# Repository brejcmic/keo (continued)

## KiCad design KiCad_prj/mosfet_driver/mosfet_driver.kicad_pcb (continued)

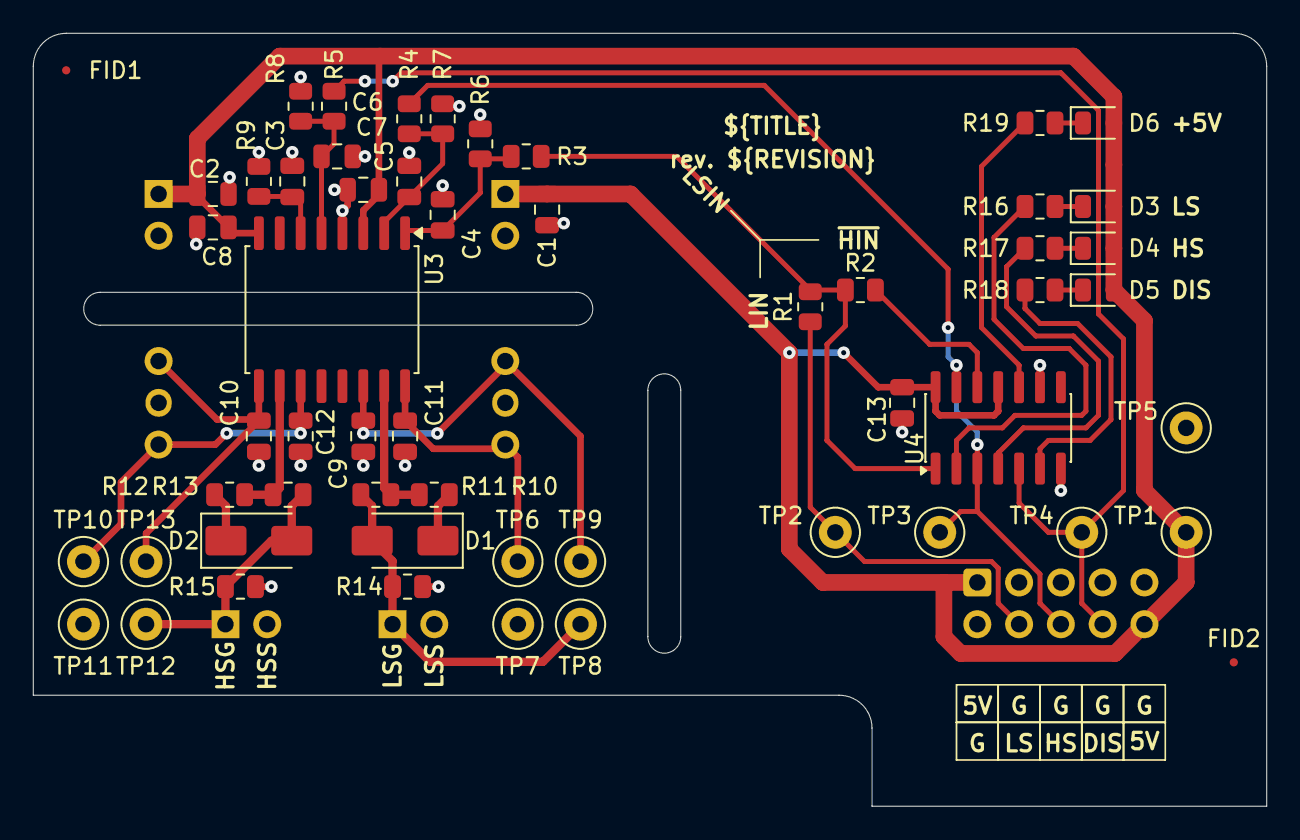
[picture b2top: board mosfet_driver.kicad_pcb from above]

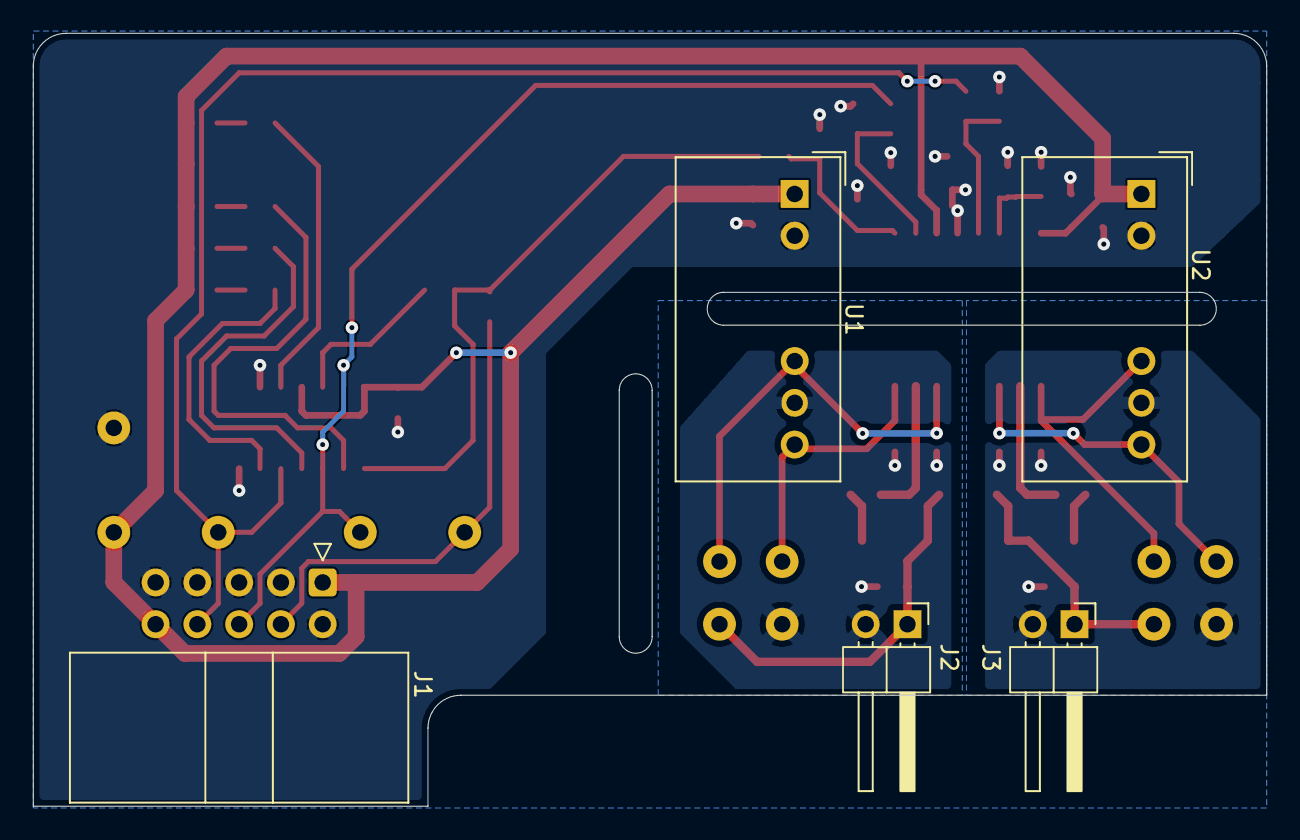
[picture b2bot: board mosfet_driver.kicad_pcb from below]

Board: 2 copper layers, 75.0 x 47.0 mm, 60 parts (5 on the bottom side), 31 nets.

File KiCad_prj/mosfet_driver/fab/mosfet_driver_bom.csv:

"Comment","Designator","Footprint","JLCPCB Part #"
"100n","C1,C2,C13","Capacitor_SMD:C_0805_2012Metric","C28233"
"470p","C3","Capacitor_SMD:C_0805_2012Metric","C1743"
"22p","C4,C5,C6","Capacitor_SMD:C_0805_2012Metric","C1804"
"1u","C7,C8,C9,C10,C11,C12","Capacitor_SMD:C_0805_2012Metric","C28323"
"SS14","D1,D2","Diode_SMD:D_SMA","C2480"
"RED","D3,D4,D5,D6,D7","LED_SMD:LED_0805_2012Metric","C84256"
"0R","R1,R2","Resistor_SMD:R_0805_2012Metric","C17477"
"100R","R3,R4,R5","Resistor_SMD:R_0805_2012Metric","C17408"
"10k","R6,R7,R8,R14,R15","Resistor_SMD:R_0805_2012Metric","C17414"
"47k","R9","Resistor_SMD:R_0805_2012Metric","C17713"
"3R3","R10,R12","Resistor_SMD:R_0805_2012Metric","C16257"
"10R","R11,R13","Resistor_SMD:R_0805_2012Metric","C17415"
"1k","R16,R17,R18,R19,R20","Resistor_SMD:R_0805_2012Metric","C17513"
"UCC21520ADW","U3","Package_SO:SOIC-16W_7.5x10.3mm_P1.27mm","C2863027"
"74HC14","U4","Package_SO:SOIC-14_3.9x8.7mm_P1.27mm","C5605"

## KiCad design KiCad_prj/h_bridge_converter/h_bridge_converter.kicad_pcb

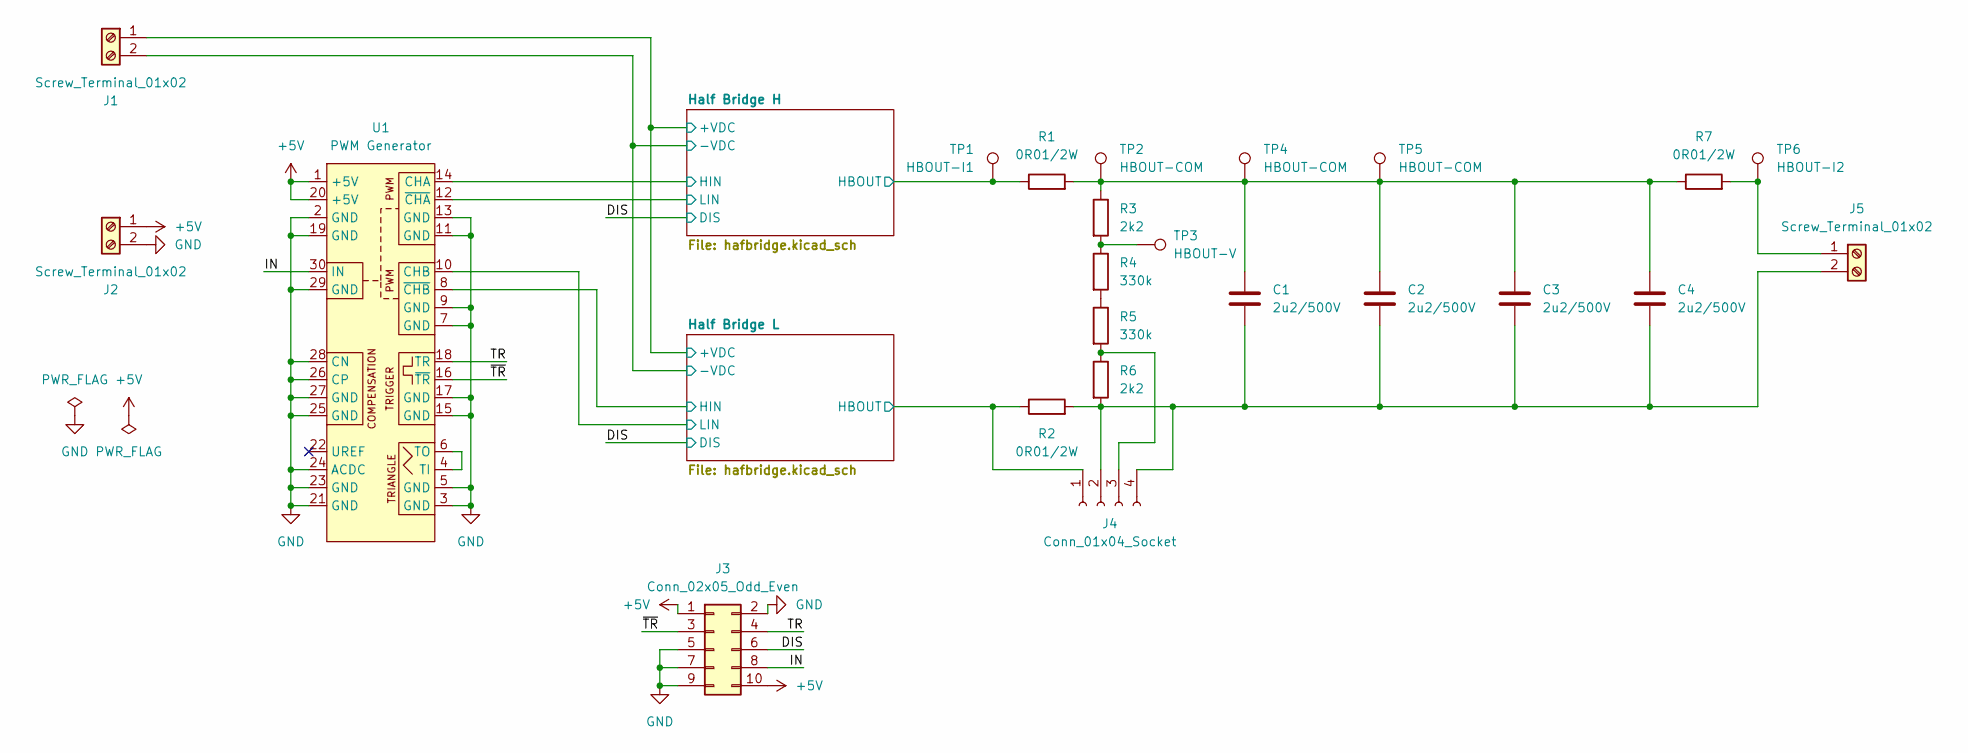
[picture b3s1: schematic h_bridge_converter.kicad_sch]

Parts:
C1, C2, C3, C4: 2u2/500V; C_Rect_L31.5mm_W13.0mm_P27.50mm_MKS4
J1, J2, J5: Screw_Terminal_01x02; TerminalBlock_WAGO_236-502_1x02_P7.50mm_45Degree
J3: Conn_02x05_Odd_Even; PinSocket_2x05_P2.54mm_Vertical
J4: Conn_01x04_Socket; PinSocket_1x04_P2.54mm_Vertical
R1, R2, R7: 0R01/2W; R_Axial_DIN0309_L9.0mm_D3.2mm_P15.24mm_Horizontal
R3, R6: 2k2; R_Axial_DIN0207_L6.3mm_D2.5mm_P7.62mm_Horizontal
R4, R5: 330k; R_Axial_DIN0207_L6.3mm_D2.5mm_P7.62mm_Horizontal
TP1: HBOUT-I1; TestPoint_Bridge_Pitch2.54mm_Drill1.0mm
TP2, TP4, TP5: HBOUT-COM; TestPoint_Bridge_Pitch2.54mm_Drill1.0mm
TP3: HBOUT-V; TestPoint_Bridge_Pitch2.54mm_Drill1.0mm
TP6: HBOUT-I2; TestPoint_Bridge_Pitch2.54mm_Drill1.0mm
U1: PWM Generator; PWMGeneratorKEO

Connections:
+5V: J2.1, J3.1, J3.10, U1.1 (+5V), U1.20 (+5V); also elsewhere on the board
/DIS: J3.6; also elsewhere on the board
/Half Bridge H/+VDC: J1.1; also elsewhere on the board
/Half Bridge H/-VDC: J1.2; also elsewhere on the board
/Half Bridge H/HBOUT: R1.1, TP1.1 (1_1); also elsewhere on the board
/Half Bridge H/HIN: U1.14 (CHA); also elsewhere on the board
/Half Bridge H/LIN: U1.12 (~CHA); also elsewhere on the board
/Half Bridge L/HBOUT: J4.1, R2.1; also elsewhere on the board
/Half Bridge L/HIN: U1.8 (~CHB); also elsewhere on the board
/Half Bridge L/LIN: U1.10 (CHB); also elsewhere on the board
/IN: J3.8, U1.30 (IN)
/TR: J3.4, U1.18 (TR)
/~TR: J3.3, U1.16 (~TR)
GND: J2.2, J3.2, J3.5, J3.7, J3.9, U1.2 (GND), U1.3 (GND), U1.5 (GND), U1.7 (GND), U1.9 (GND), U1.11 (GND), U1.13 (GND), U1.15 (GND), U1.17 (GND), U1.19 (GND), U1.21 (GND), U1.23 (GND), U1.24 (ACDC), U1.25 (GND), U1.26 (CP), U1.27 (GND), U1.28 (CN), U1.29 (GND); also elsewhere on the board
unnamed: C1.1, C2.1, C3.1, C4.1, R1.2, R3.1, R7.1, TP2.1 (1_1), TP4.1 (1_1), TP5.1 (1_1)
unnamed: C1.2, C2.2, C3.2, C4.2, J4.2, J4.4, J5.2, R2.2, R6.2
unnamed: J4.3, R5.2, R6.1
unnamed: J5.1, R7.2, TP6.1 (1_1)
unnamed: R3.2, R4.1, TP3.1 (1_1)
unnamed: R4.2, R5.1
unnamed: U1.4 (TI), U1.6 (TO)

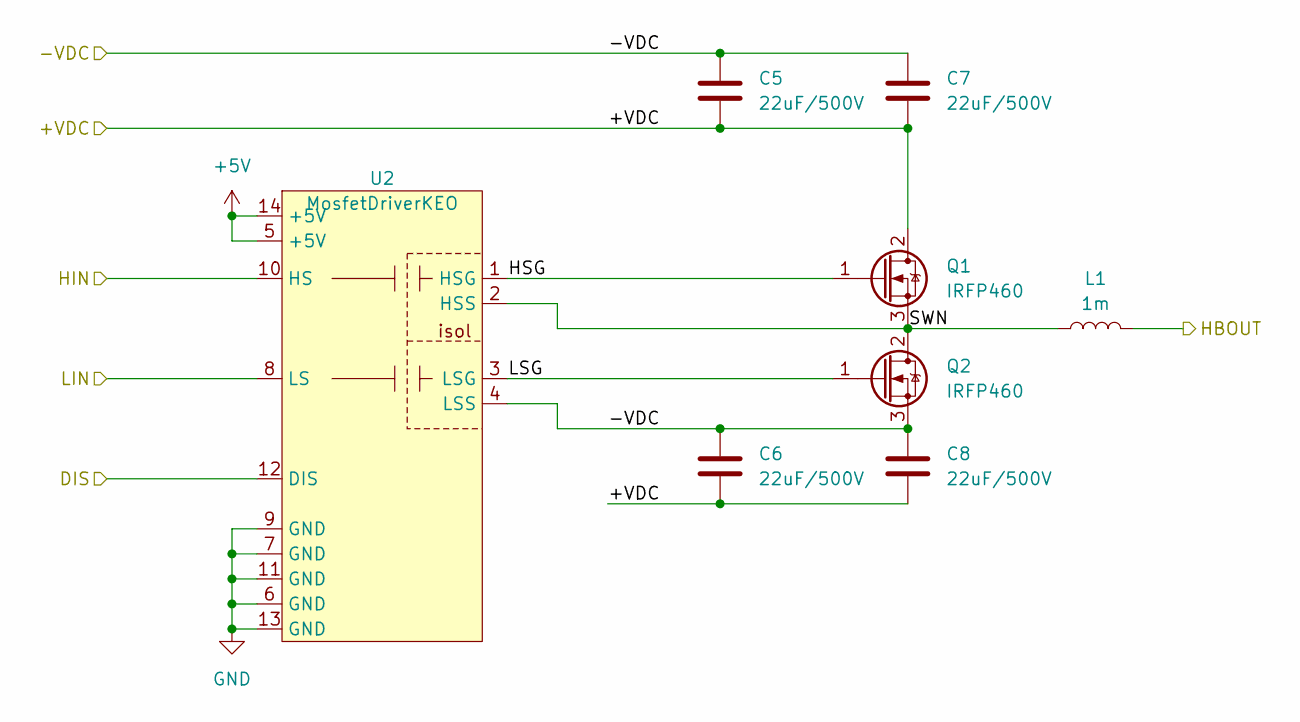
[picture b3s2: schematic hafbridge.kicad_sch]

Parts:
C5, C6, C7, C8: 22uF/500V; C_Rect_L31.5mm_W20.0mm_P27.50mm_MKS4
L1: 1m; L_Toroid_Vertical_L54.0mm_W23.8mm_P20.10mm_Bourns_5700
Q1, Q2: IRFP460; TO-247-3_Horizontal
U2: MosfetDriverKEO; Mosfet_Driver_KEO

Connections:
+5V: U2.5 (+5V), U2.14 (+5V); also elsewhere on the board
/DIS: U2.12 (DIS); also elsewhere on the board
/Half Bridge H/+VDC: C5.2, C6.2, C7.2, C8.2, Q1.2 (D); also elsewhere on the board
/Half Bridge H/-VDC: C5.1, C6.1, C7.1, C8.1, Q2.3 (S), U2.4 (LSS); also elsewhere on the board
/Half Bridge H/HBOUT: L1.2; also elsewhere on the board
/Half Bridge H/HIN: U2.10 (HS); also elsewhere on the board
/Half Bridge H/HSG: Q1.1 (G), U2.1 (HSG)
/Half Bridge H/LIN: U2.8 (LS); also elsewhere on the board
/Half Bridge H/LSG: Q2.1 (G), U2.3 (LSG)
/Half Bridge H/SWN: L1.1, Q1.3 (S), Q2.2 (D), U2.2 (HSS)
GND: U2.6 (GND), U2.7 (GND), U2.9 (GND), U2.11 (GND), U2.13 (GND); also elsewhere on the board

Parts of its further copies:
C9, C10, C11, C12: 22uF/500V; C_Rect_L31.5mm_W20.0mm_P27.50mm_MKS4
L2: 1m; L_Toroid_Vertical_L54.0mm_W23.8mm_P20.10mm_Bourns_5700
Q3, Q4: IRFP460; TO-247-3_Horizontal
U3: MosfetDriverKEO; Mosfet_Driver_KEO

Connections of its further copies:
+5V: U3.5 (+5V), U3.14 (+5V); also elsewhere on the board
/DIS: U3.12 (DIS); also elsewhere on the board
/Half Bridge H/+VDC: C9.2, C10.2, C11.2, C12.2, Q3.2 (D); also elsewhere on the board
/Half Bridge H/-VDC: C9.1, C10.1, C11.1, C12.1, Q4.3 (S), U3.4 (LSS); also elsewhere on the board
/Half Bridge L/HBOUT: L2.2; also elsewhere on the board
/Half Bridge L/HIN: U3.10 (HS); also elsewhere on the board
/Half Bridge L/HSG: Q3.1 (G), U3.1 (HSG)
/Half Bridge L/LIN: U3.8 (LS); also elsewhere on the board
/Half Bridge L/LSG: Q4.1 (G), U3.3 (LSG)
/Half Bridge L/SWN: L2.1, Q3.3 (S), Q4.2 (D), U3.2 (HSS)
GND: U3.6 (GND), U3.7 (GND), U3.9 (GND), U3.11 (GND), U3.13 (GND); also elsewhere on the board

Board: 2 copper layers, 39 parts (4 on the bottom side), 27 nets, no tracks yet.

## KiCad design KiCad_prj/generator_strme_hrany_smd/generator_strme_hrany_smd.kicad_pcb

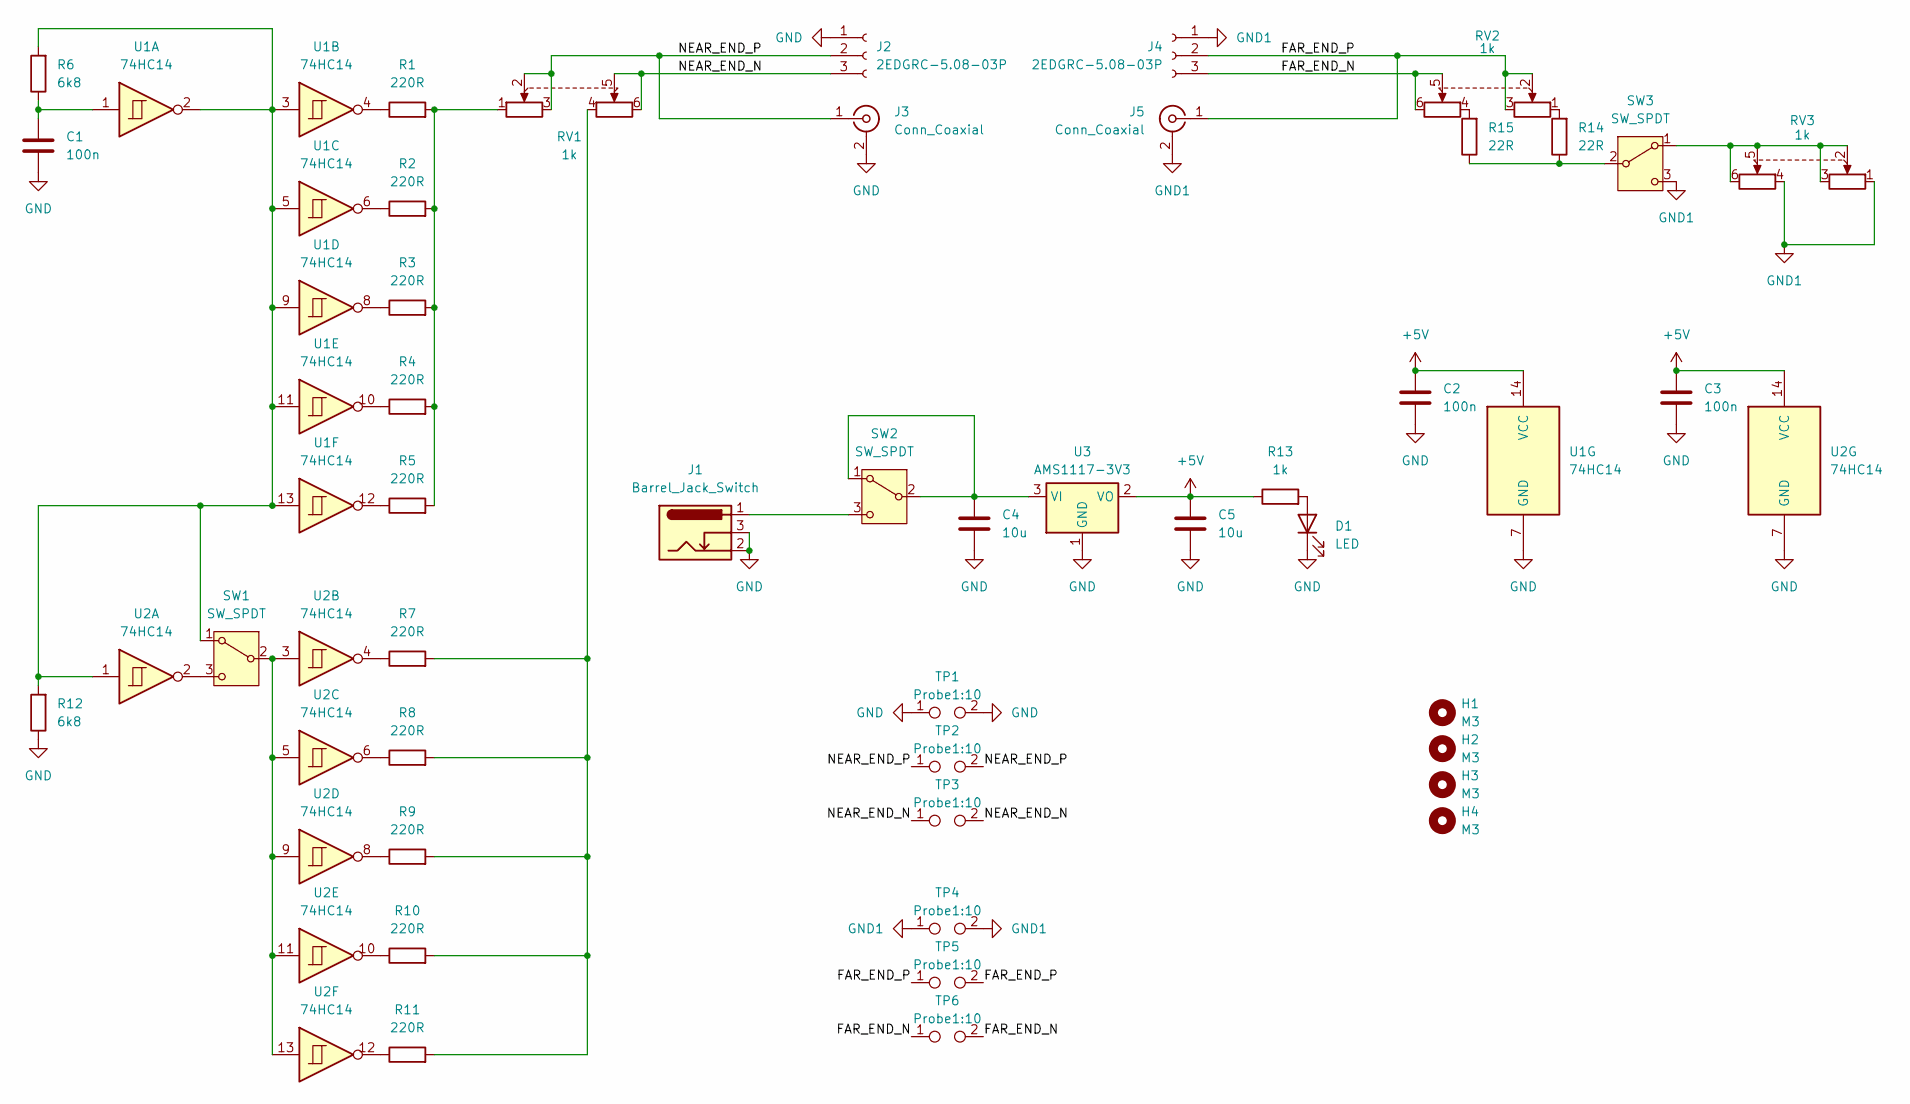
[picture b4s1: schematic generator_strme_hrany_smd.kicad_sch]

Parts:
C1, C2, C3: 100n; C_0805_2012Metric
C4, C5: 10u; C_0805_2012Metric
D1: LED; LED_0805_2012Metric
H1, H2, H3, H4: M3; MountingHole_3.2mm_M3_ISO7380
J1: Barrel_Jack_Switch; BarrelJack_GCT_DCJ200-10-A_Horizontal
J2, J4: 2EDGRC-5.08-03P; PhoenixContact_MSTBA_2,5_3-G-5,08_1x03_P5.08mm_Horizontal
J3, J5: Conn_Coaxial; BNC_Amphenol_B6252HB-NPP3G-50_Horizontal
R1, R2, R3, R4, R5, R7, R8, R9, R10, R11: 220R; R_0805_2012Metric
R6, R12: 6k8; R_0805_2012Metric
R13: 1k; R_0805_2012Metric
R14, R15: 22R; R_0805_2012Metric
RV1, RV2, RV3: 1k; Potentiometer_Alpha_RD902F-40-00D_Dual_Vertical
SW1, SW2, SW3: SW_SPDT; KLS7-SS02-12F20
TP1, TP2, TP3, TP4, TP5, TP6: Probe1:10; TestPoint_2Pads_Pitch2.54mm_Drill0.8mm
U1, U2: 74HC14; DIP-14_W7.62mm_LongPads
U3: AMS1117-3V3; SOT-223-3_TabPin2

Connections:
+5V: C2.1, C3.1, C5.1, R13.1, U1.14 (VCC), U2.14 (VCC), U3.2 (VO)
/FAR_END_N: J4.3, RV2.5, RV2.6, TP6.1, TP6.2
/FAR_END_P: J4.2, J5.1 (In), RV2.2, RV2.3, TP5.1, TP5.2
/NEAR_END_N: J2.3, RV1.5, RV1.6, TP3.1, TP3.2
/NEAR_END_P: J2.2, J3.1 (In), RV1.2, RV1.3, TP2.1, TP2.2
GND: C1.2, C2.2, C3.2, C4.2, C5.2, D1.1 (K), J1.2, J1.3, J2.1, J3.2 (Ext), R12.1, TP1.1, TP1.2, U1.7 (GND), U2.7 (GND), U3.1 (GND)
GND1: J4.1, J5.2 (Ext), RV3.1, RV3.4, SW3.3 (C), TP4.1, TP4.2
unnamed: C1.1, R6.1, U1.1
unnamed: D1.2 (A), R13.2
unnamed: R1.1, U1.4
unnamed: R1.2, R2.2, R3.2, R4.2, R5.2, RV1.1
unnamed: R2.1, U1.6
unnamed: R3.1, U1.8
unnamed: R4.1, U1.10
unnamed: R5.1, U1.12
unnamed: R7.1, U2.4
unnamed: R8.1, U2.6
unnamed: R9.1, U2.8
unnamed: R10.1, U2.10
unnamed: R7.2, R8.2, R9.2, R10.2, R11.2, RV1.4
unnamed: R11.1, U2.12
unnamed: R14.2, RV2.1
unnamed: R15.2, RV2.4
unnamed: R6.2, R12.2, SW1.1 (A), U1.2, U1.3, U1.5, U1.9, U1.11, U1.13, U2.1
unnamed: SW1.2 (B), U2.3, U2.5, U2.9, U2.11, U2.13
unnamed: SW1.3 (C), U2.2
unnamed: C4.1, SW2.1 (A), SW2.2 (B), U3.3 (VI)
unnamed: J1.1, SW2.3 (C)
unnamed: RV3.2, RV3.3, RV3.5, RV3.6, SW3.1 (A)
unnamed: R14.1, R15.1, SW3.2 (B)

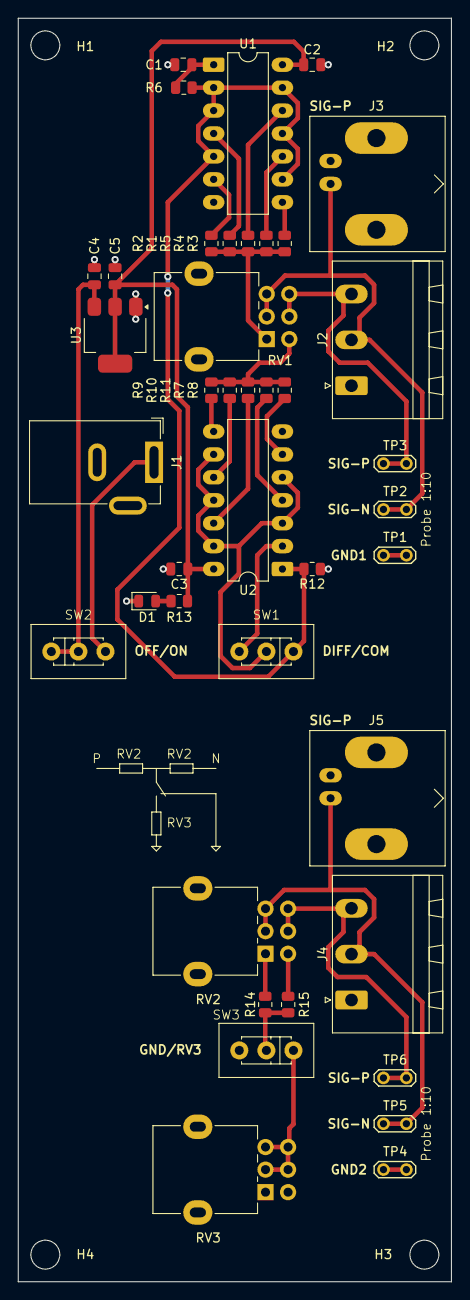
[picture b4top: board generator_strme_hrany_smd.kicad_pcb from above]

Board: 2 copper layers, 48.0 x 140.0 mm, 45 parts (0 on the bottom side), 30 nets.

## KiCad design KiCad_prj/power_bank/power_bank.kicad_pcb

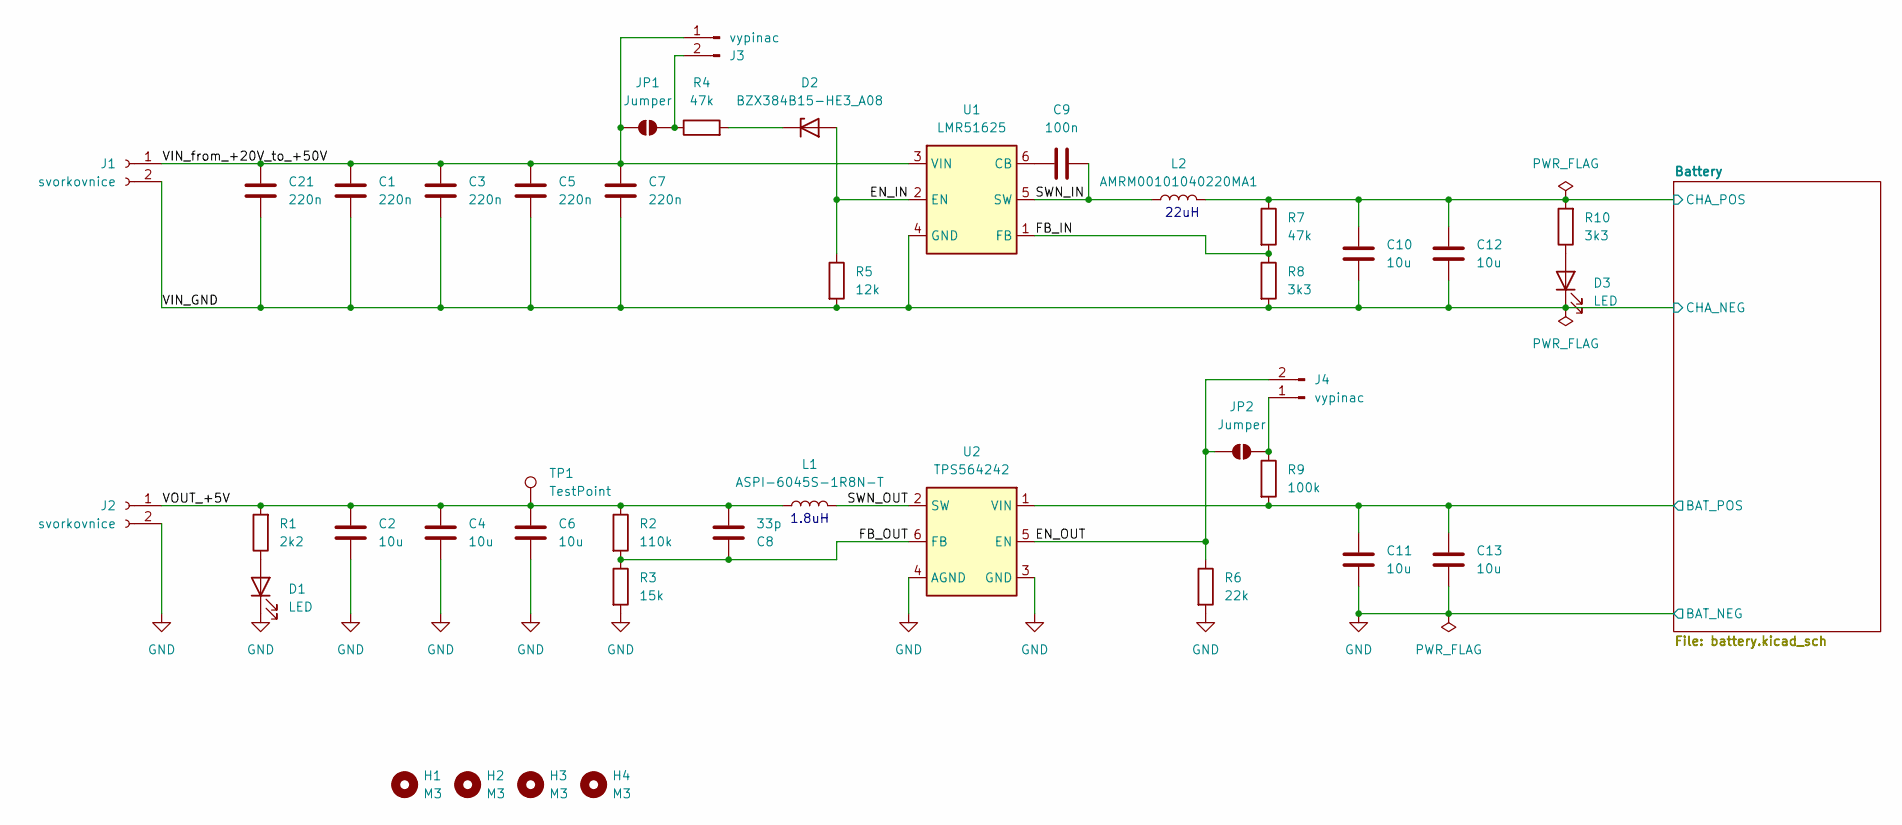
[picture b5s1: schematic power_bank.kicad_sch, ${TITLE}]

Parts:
C1, C3, C5, C7, C21: 220n; C_0805_2012Metric; JLCPCB Part # C6119933
C2, C4, C6, C10, C11, C12, C13: 10u; C_0805_2012Metric; JLCPCB Part # C15850
C8: 33p; C_0805_2012Metric; JLCPCB Part # C107115
C9: 100n; C_0805_2012Metric; JLCPCB Part # C28233
D1, D3: LED; LED_D3.0mm
D2: BZX384B15-HE3_A08; D_SOD-323F; JLCPCB Part # C49296788
H1, H2, H3, H4: M3; MountingHole_3.2mm_M3
J1, J2: svorkovnice; PhoenixContact_MSTBVA_2,5_2-G-5,08_1x02_P5.08mm_Vertical
J3, J4: vypinac; PinHeader_1x02_P2.54mm_Vertical
JP1, JP2: Jumper; SolderJumper-2_P1.3mm_Open_RoundedPad1.0x1.5mm
L1: ASPI-6045S-1R8N-T; L_APV_ANR6045; JLCPCB Part # C2997654
L2: AMRM00101040220MA1; L_10.4x10.4_H4.8; JLCPCB Part # C10165
R1: 2k2; R_0805_2012Metric; JLCPCB Part # C17520
R2: 110k; R_0805_2012Metric; JLCPCB Part # C17422
R3: 15k; R_0805_2012Metric; JLCPCB Part # C17475
R4, R7: 47k; R_0805_2012Metric; JLCPCB Part # C17713
R5: 12k; R_0805_2012Metric; JLCPCB Part # C17444
R6: 22k; R_0805_2012Metric; JLCPCB Part # C17560
R8, R10: 3k3; R_0805_2012Metric; JLCPCB Part # C26010
R9: 100k; R_0805_2012Metric; JLCPCB Part # C149504
TP1: TestPoint; TestPoint_Pad_D2.0mm
U1: LMR51625; SOT-23-6; JLCPCB Part # C45262767
U2: TPS564242; SOT-563; JLCPCB Part # C5219267

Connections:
/Battery/BAT_POS: C11.1, C13.1, R9.2, U2.1 (VIN); also elsewhere on the board
/Battery/CHA_POS: C10.1, C12.1, L2.2, R7.1, R10.2; also elsewhere on the board
/EN_IN: D2.2 (A), R5.1, U1.2 (EN)
/EN_OUT: J4.2, JP2.1 (A), R6.1, U2.5 (EN)
/FB_IN: R7.2, R8.1, U1.1 (FB)
/FB_OUT: C8.2, R2.2, R3.1, U2.6 (FB)
/SWN_IN: C9.2, L2.1, U1.5 (SW)
/SWN_OUT: L1.2, U2.2 (SW)
/VIN_GND: C1.2, C3.2, C5.2, C7.2, C10.2, C12.2, C21.2, D3.1 (K), J1.2, R5.2, R8.2, U1.4 (GND); also elsewhere on the board
/VIN_from_+20V_to_+50V: C1.1, C3.1, C5.1, C7.1, C21.1, J1.1, J3.1, JP1.1 (A), U1.3 (VIN)
/VOUT_+5V: C2.1, C4.1, C6.1, C8.1, J2.1, L1.1, R1.2, R2.1, TP1.1
GND: C2.2, C4.2, C6.2, C11.2, C13.2, D1.1 (K), J2.2, R3.2, R6.2, U2.3 (GND), U2.4 (AGND); also elsewhere on the board
unnamed: D1.2 (A), R1.1
unnamed: D2.1 (K), R4.2
unnamed: D3.2 (A), R10.1
unnamed: J3.2, JP1.2 (B), R4.1
unnamed: J4.1, JP2.2 (B), R9.1
unnamed: C9.1, U1.6 (CB)

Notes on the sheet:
1.8uH
22uH

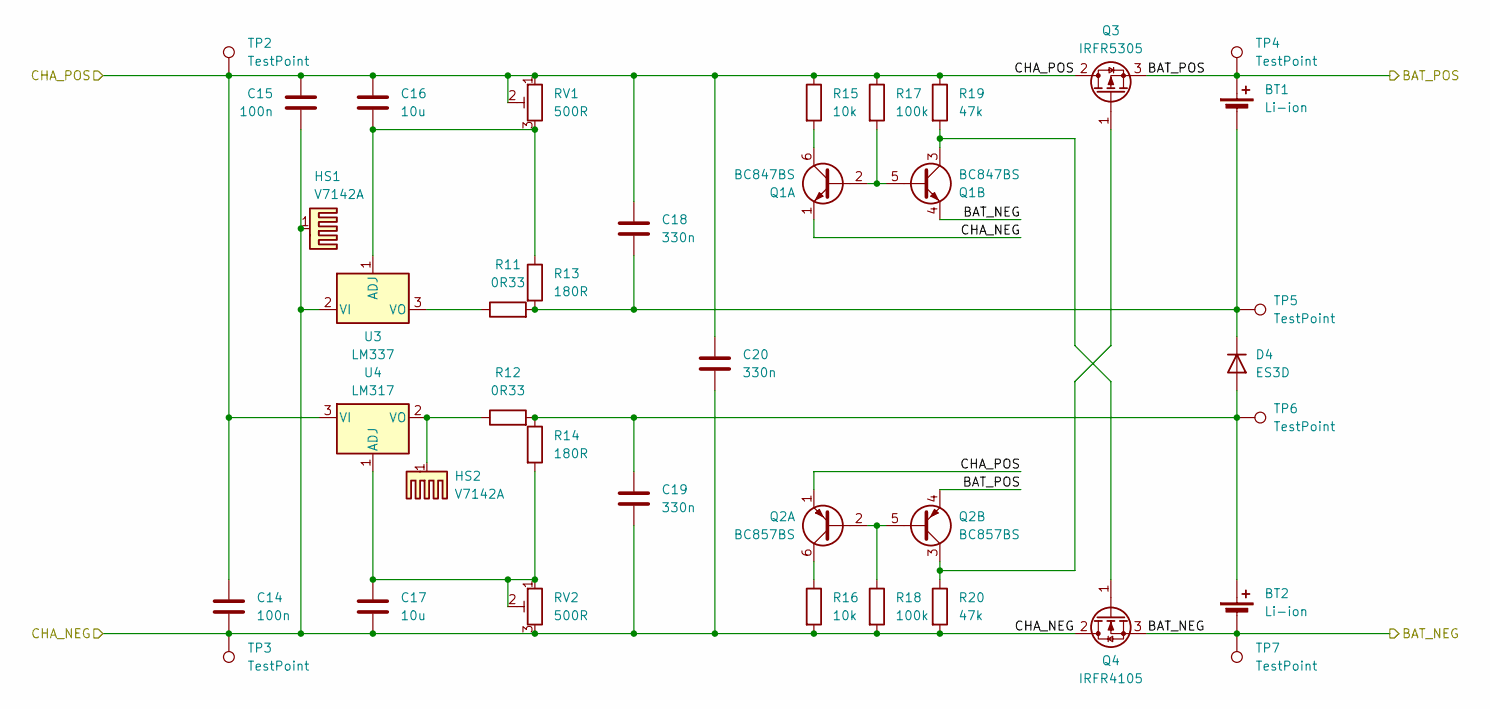
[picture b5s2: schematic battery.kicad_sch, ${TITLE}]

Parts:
BT1, BT2: Li-ion; BatteryHolder_MPD_BH-18650-PC
C14, C15: 100n; C_0805_2012Metric; JLCPCB Part # C28233
C16, C17: 10u; C_0805_2012Metric; JLCPCB Part # C15850
C18, C19, C20: 330n; C_0805_2012Metric; JLCPCB Part # C1740
D4: ES3D; D_SMC; JLCPCB Part # C16235
HS1, HS2: V7142A
Q1: BC847BS; SOT-363_SC-70-6; JLCPCB Part # C8653
Q2: BC857BS; SOT-363_SC-70-6; JLCPCB Part # C8654
Q3: IRFR5305; TO-252-2; JLCPCB Part # C2624
Q4: IRFR4105; TO-252-2; JLCPCB Part # C22366766
R11, R12: 0R33; R_Axial_DIN0411_L9.9mm_D3.6mm_P12.70mm_Horizontal
R13, R14: 180R; R_0805_2012Metric; JLCPCB Part # C1339
R15, R16: 10k; R_0805_2012Metric; JLCPCB Part # C17414
R17, R18: 100k; R_0805_2012Metric; JLCPCB Part # C149504
R19, R20: 47k; R_0805_2012Metric; JLCPCB Part # C17713
RV1, RV2: 500R; Potentiometer_ACP_CA9-V10_Vertical
TP2, TP3, TP4, TP5, TP6, TP7: TestPoint; TestPoint_Pad_D2.0mm
U3: LM337; TO-220-3_Vertical
U4: LM317; TO-220-3_Vertical

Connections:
/Battery/BAT_POS: BT1.1 (+), Q2.4 (E2), Q3.3 (S), TP4.1; also elsewhere on the board
/Battery/CHA_POS: C14.1, C15.1, C16.1, C18.1, C20.1, Q2.1 (E1), Q3.2 (D), R15.1, R17.1, R19.1, RV1.1, RV1.2, TP2.1, U4.3 (VI); also elsewhere on the board
/VIN_GND: C14.2, C15.2, C17.2, C19.2, C20.2, HS1.1, Q1.1 (E1), Q4.2 (D), R16.2, R18.2, R20.2, RV2.3, TP3.1, U3.2 (VI); also elsewhere on the board
GND: BT2.2 (-), Q1.4 (E2), Q4.3 (S), TP7.1; also elsewhere on the board
unnamed: BT1.2 (-), C18.2, D4.1 (K), R11.2, R13.2, TP5.1
unnamed: BT2.1 (+), C19.1, D4.2 (A), R12.2, R14.1, TP6.1
unnamed: Q1.2 (B1), Q1.5 (B2), R17.2
unnamed: Q1.6 (C1), R15.2
unnamed: Q1.3 (C2), Q4.1 (G), R19.2
unnamed: Q2.2 (B1), Q2.5 (B2), R18.1
unnamed: Q2.6 (C1), R16.1
unnamed: Q2.3 (C2), Q3.1 (G), R20.1
unnamed: C16.2, R13.1, RV1.3, U3.1 (ADJ)
unnamed: R11.1, U3.3 (VO)
unnamed: C17.1, R14.2, RV2.1, RV2.2, U4.1 (ADJ)
unnamed: HS2.1, R12.1, U4.2 (VO)

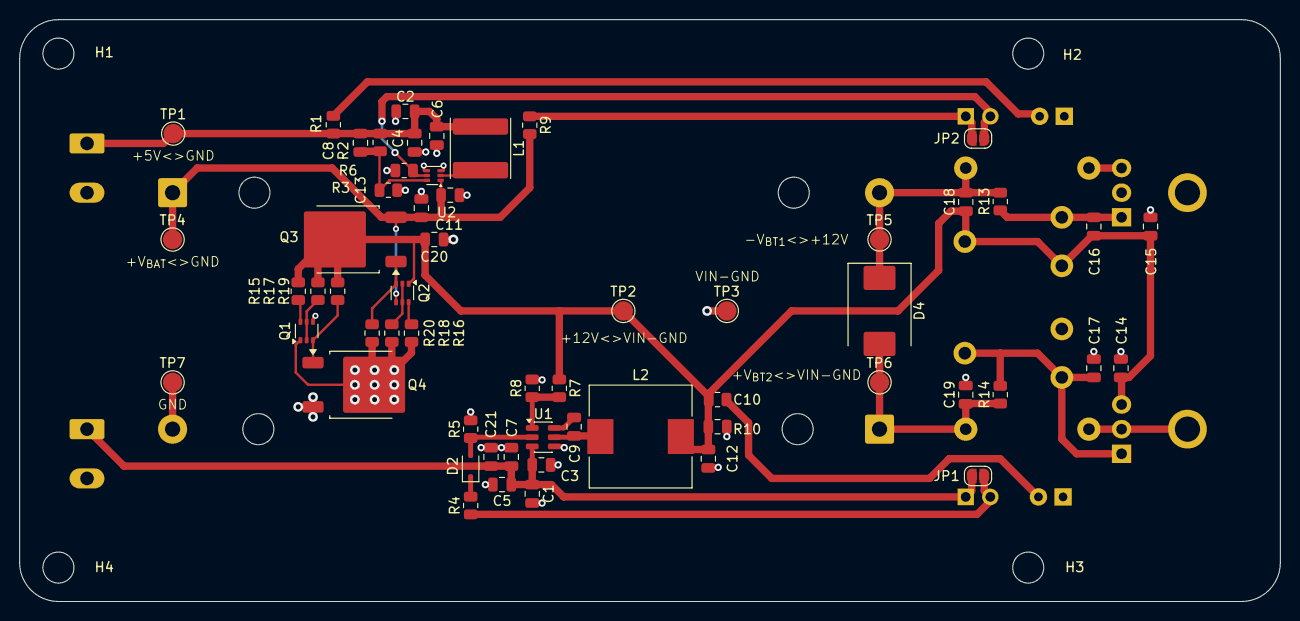
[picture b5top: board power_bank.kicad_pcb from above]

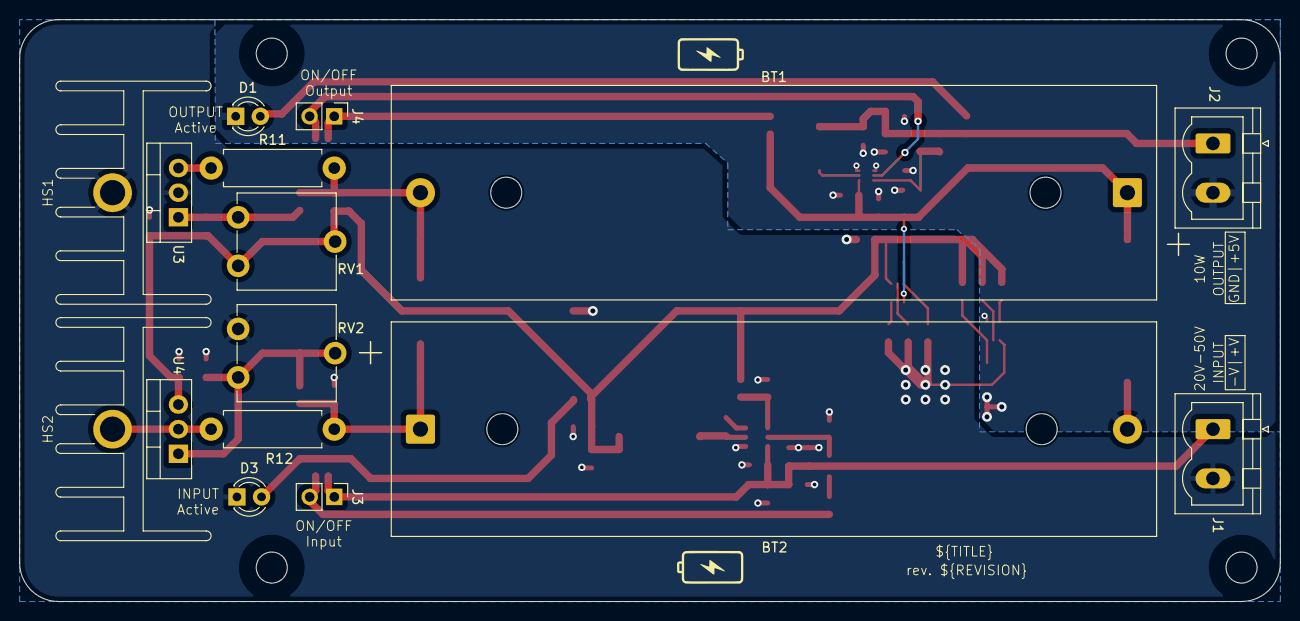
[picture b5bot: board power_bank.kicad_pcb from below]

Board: 2 copper layers, 130.0 x 60.0 mm, 78 parts (16 on the bottom side), 30 nets.

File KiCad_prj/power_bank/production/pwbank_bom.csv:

"Reference","Value","Footprint","JLCPCB Part #"
"C1,C3,C5,C7,C21","220n","Capacitor_SMD:C_0805_2012Metric","C6119933"
"C2,C4,C6,C10,C11,C12,C13,C16,C17","10u","Capacitor_SMD:C_0805_2012Metric","C15850"
"C8","33p","Capacitor_SMD:C_0805_2012Metric","C107115"
"C9,C14,C15","100n","Capacitor_SMD:C_0805_2012Metric","C28233"
"C18,C19,C20","330n","Capacitor_SMD:C_0805_2012Metric","C1740"
"D2","BZX384B15-HE3_A08","Diode_SMD:D_SOD-323F","C49296788"
"D4","ES3D","Diode_SMD:D_SMC","C16235"
"L1","ASPI-6045S-1R8N-T","Inductor_SMD:L_APV_ANR6045","C2997654"
"L2","AMRM00101040220MA1","Inductor_SMD:L_10.4x10.4_H4.8","C10165"
"Q1","BC847BS","Package_TO_SOT_SMD:SOT-363_SC-70-6","C8653"
"Q2","BC857BS","Package_TO_SOT_SMD:SOT-363_SC-70-6","C8654"
"Q3","IRFR5305","Package_TO_SOT_SMD:TO-252-2","C2624"
"Q4","IRFR4105","Package_TO_SOT_SMD:TO-252-2","C22366766"
"R1","2k2","Resistor_SMD:R_0805_2012Metric","C17520"
"R2","110k","Resistor_SMD:R_0805_2012Metric","C4310"
"R3","15k","Resistor_SMD:R_0805_2012Metric","C17475"
"R4,R7,R19,R20","47k","Resistor_SMD:R_0805_2012Metric","C17713"
"R5","12k","Resistor_SMD:R_0805_2012Metric","C17444"
"R6","22k","Resistor_SMD:R_0805_2012Metric","C17560"
"R8,R10","3k3","Resistor_SMD:R_0805_2012Metric","C26010"
"R9,R17,R18","100k","Resistor_SMD:R_0805_2012Metric","C149504"
"R13,R14","180R","Resistor_SMD:R_0805_2012Metric","C1339"
"R15,R16","10k","Resistor_SMD:R_0805_2012Metric","C17414"
"U1","LMR51625","Package_TO_SOT_SMD:SOT-23-6","C45262767"
"U2","TPS564242","Package_TO_SOT_SMD:SOT-563","C5219267"

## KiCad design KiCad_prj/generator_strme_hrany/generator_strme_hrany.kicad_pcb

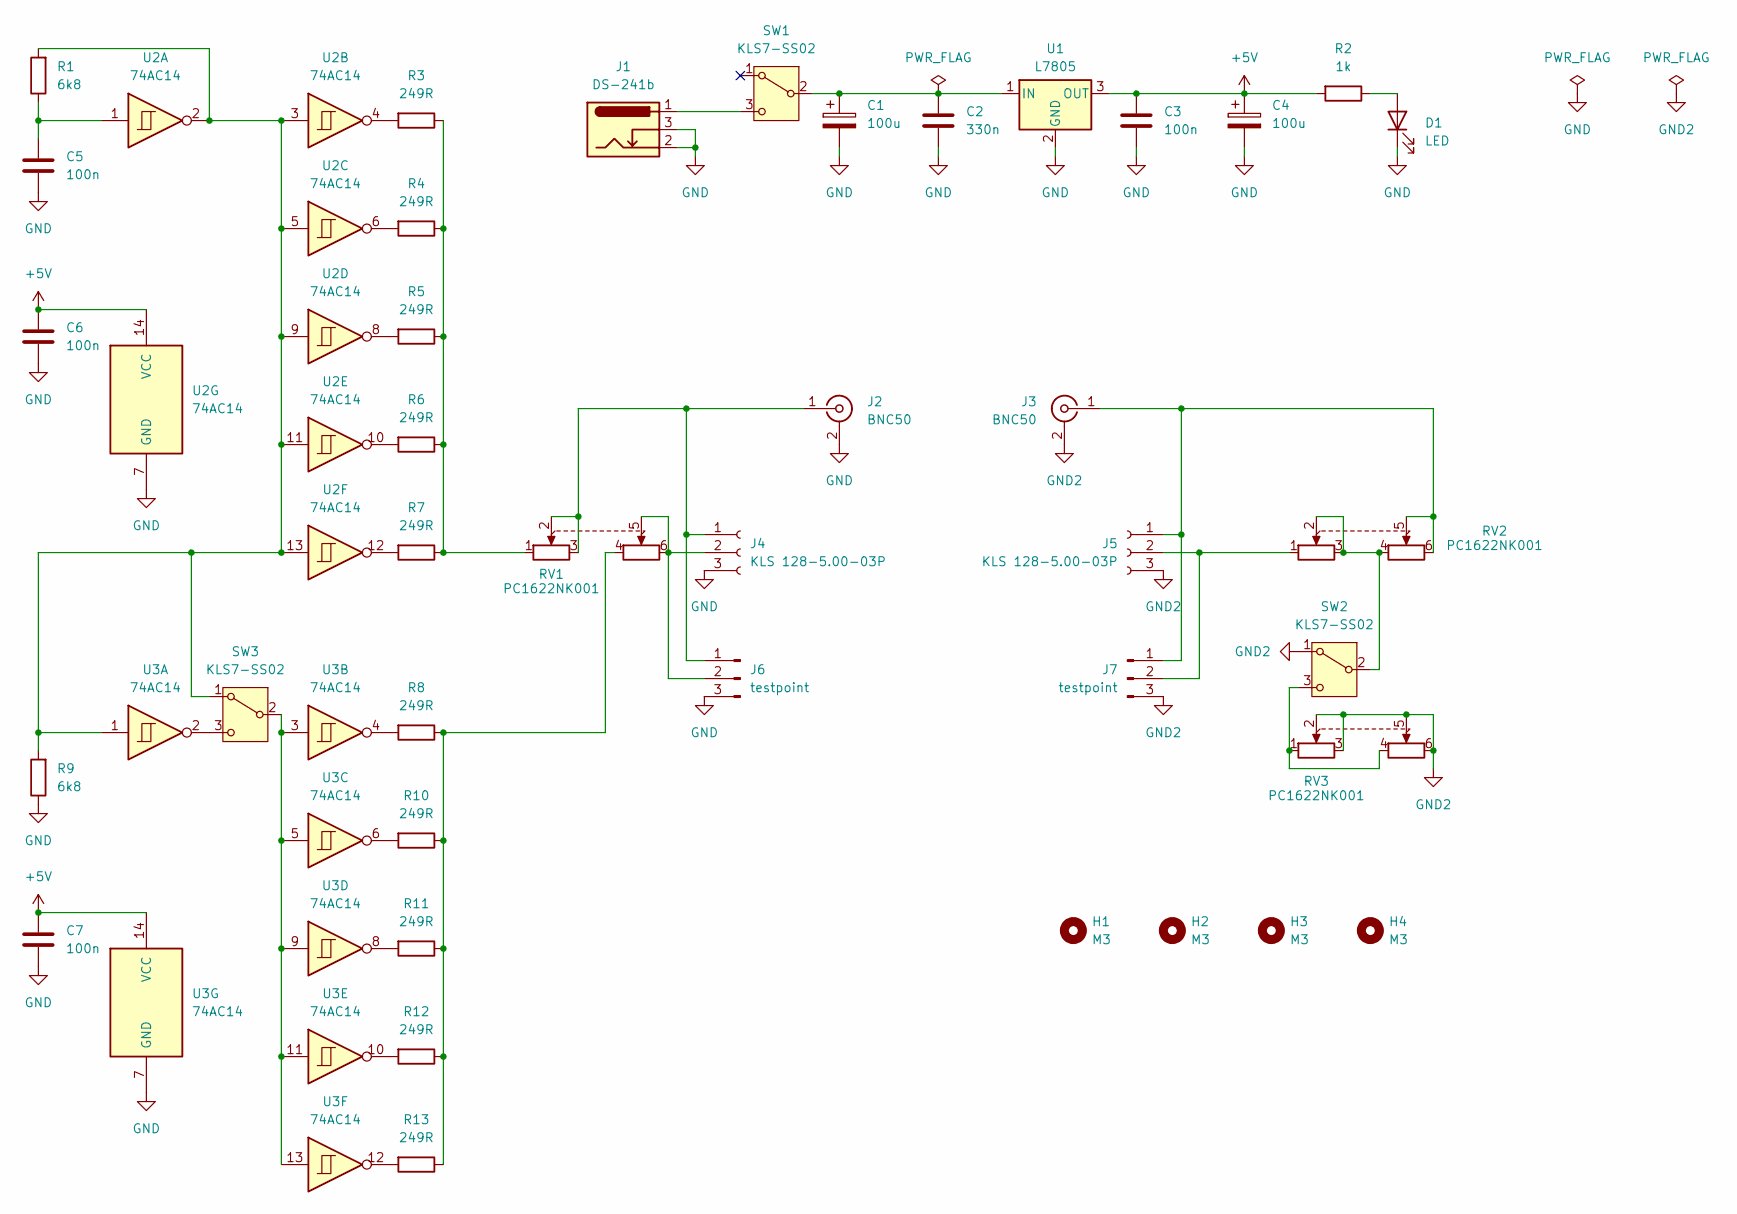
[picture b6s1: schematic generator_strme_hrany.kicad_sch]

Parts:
C1, C4: 100u; CP_Radial_D6.3mm_P2.50mm
C2: 330n; C_Rect_L7.0mm_W2.5mm_P5.00mm
C3, C5, C6, C7: 100n; C_Rect_L7.0mm_W2.5mm_P5.00mm
D1: LED; LED_D3.0mm
H1, H2, H3, H4: M3; MountingHole_3.2mm_M3
J1: DS-241b; BarrelJack_GCT_DCJ200-10-A_Horizontal
J2, J3: BNC50; BNC_Amphenol_B6252HB-NPP3G-50_Horizontal
J4, J5: KLS 128-5.00-03P; JST_NV_B03P-NV_1x03_P5.00mm_Vertical
J6, J7: testpoint; SolderWire-1sqmm_1x03_P5.4mm_D1.4mm_OD2.7mm
R1, R9: 6k8; R_Axial_DIN0207_L6.3mm_D2.5mm_P7.62mm_Horizontal
R2: 1k; R_Axial_DIN0207_L6.3mm_D2.5mm_P7.62mm_Horizontal
R3, R4, R5, R6, R7, R8, R10, R11, R12, R13: 249R; R_Axial_DIN0207_L6.3mm_D2.5mm_P7.62mm_Horizontal
RV1, RV2, RV3: PC1622NK001; Potentiometer_Alps_RK163_Dual_Horizontal
SW1, SW2, SW3: KLS7-SS02; KLS7-SS02-12F20
U1: L7805; TO-220-3_Horizontal_TabDown
U2, U3: 74AC14; CERDIP-14_W7.62mm_SideBrazed_LongPads

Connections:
+5V: C3.1, C4.1, C6.1, C7.1, R2.2, U1.3 (OUT), U2.14 (VCC), U3.14 (VCC)
GND: C1.2, C2.2, C3.2, C4.2, C5.2, C6.2, C7.2, D1.1 (K), J1.2, J1.3, J2.2 (Ext), J4.3, J6.3, R9.1, U1.2 (GND), U2.7 (GND), U3.7 (GND)
GND2: J3.2 (Ext), J5.3, J7.3, RV3.2, RV3.3, RV3.5, RV3.6, SW2.1 (A)
unnamed: C5.1, R1.1, U2.1
unnamed: D1.2 (A), R2.1
unnamed: J2.1 (In), J4.1, J6.1, RV1.2, RV1.3
unnamed: J3.1 (In), J5.1, J7.1, RV2.5, RV2.6
unnamed: J4.2, J6.2, RV1.5, RV1.6
unnamed: J5.2, J7.2, RV2.1
unnamed: R3.1, R4.1, R5.1, R6.1, R7.1, RV1.1
unnamed: R3.2, U2.4
unnamed: R4.2, U2.6
unnamed: R5.2, U2.8
unnamed: R6.2, U2.10
unnamed: R7.2, U2.12
unnamed: R8.2, U3.4
unnamed: R8.1, R10.1, R11.1, R12.1, R13.1, RV1.4
unnamed: R10.2, U3.6
unnamed: R11.2, U3.8
unnamed: R12.2, U3.10
unnamed: R13.2, U3.12
unnamed: C1.1, C2.1, SW1.2 (B), U1.1 (IN)
unnamed: J1.1, SW1.3 (C)
unnamed: RV2.2, RV2.3, RV2.4, SW2.2 (B)
unnamed: RV3.1, RV3.4, SW2.3 (C)
unnamed: R1.2, R9.2, SW3.1 (A), U2.2, U2.3, U2.5, U2.9, U2.11, U2.13, U3.1
unnamed: SW3.2 (B), U3.3, U3.5, U3.9, U3.11, U3.13
unnamed: SW3.3 (C), U3.2
